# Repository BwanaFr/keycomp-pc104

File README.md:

# keycomp-pc104
A PC/104 compatible motherboard for Keycomp 386SX computer

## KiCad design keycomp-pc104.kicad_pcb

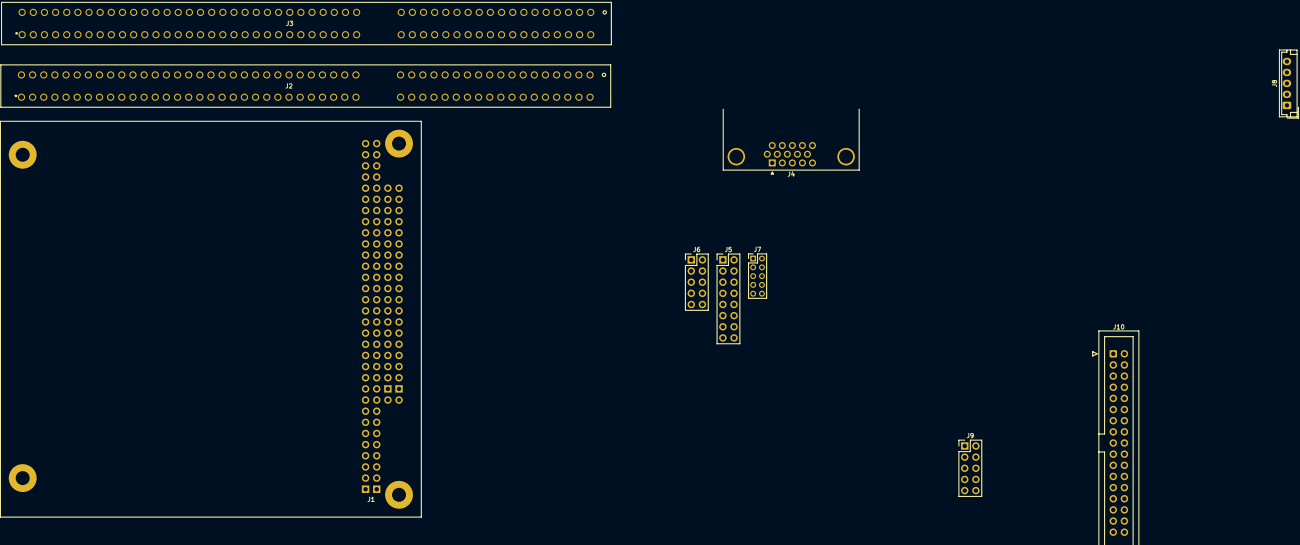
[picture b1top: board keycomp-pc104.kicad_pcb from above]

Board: 2 copper layers, 10 parts (0 on the bottom side), 101 nets, no tracks yet.

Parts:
J1: Bus_PC104_16bit; PC104_16bit
J2, J3: Bus_ISA_16bit; EBC49DCWN-S420
J4: VGA; DSUB-15-HD_Female_Horizontal_P2.29x1.98mm_EdgePinOffset8.35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
J5: VGA_PCM; PinHeader_2x08_P2.54mm_Vertical
J6: X10_KONTRON; PinHeader_2x05_P2.54mm_Vertical
J7: VGA_VORTEX; PinHeader_2x05_P2.00mm_Vertical
J8: KEYBOARD; JST_EH_B5B-EH-A_1x05_P2.50mm_Vertical
J9: X31_KONTRON; PinHeader_2x05_P2.54mm_Vertical
J10: FLOPPY; IDC-Header_2x17_P2.54mm_Vertical

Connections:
+5V: J1.B3 (+5V), J1.B29 (+5V), J1.D16 (+5V), J2.3 (+5V), J2.29 (VCC), J2.78 (+5V), J3.3 (+5V), J3.29 (VCC), J3.78 (+5V), J8.4
+12V: J1.B9 (+12V), J2.9 (+12V), J3.9 (+12V)
-5V: J1.B5 (-5V), J2.5 (-5V), J3.5 (-5V)
-12V: J1.B7 (-12V), J2.7 (-12V), J3.7 (-12V)
/IO ports/KB_CLK: J8.1, J9.6
/IO ports/KB_DATA: J8.2, J9.5
/IO ports/VGA_BLUE: J4.3, J5.5, J6.6, J7.5
/IO ports/VGA_GREEN: J4.2, J5.3, J6.4, J7.3
/IO ports/VGA_HSYNC: J4.13, J5.10, J6.8, J7.7
/IO ports/VGA_RED: J4.1, J5.1, J6.2, J7.1
/IO ports/VGA_SCL: J4.15, J6.10
/IO ports/VGA_SDA: J4.12, J6.7
/IO ports/VGA_VSYNC: J4.14, J5.12, J6.9, J7.9
AEN: J1.A11 (AEN), J2.42 (AEN), J3.42 (AEN)
BALE: J1.B28 (BALE), J2.28 (ALE), J3.28 (ALE)
BCLK: J1.B20 (BCLK), J2.20 (CLK), J3.20 (CLK)
DRQ0: J1.D9 (DRQ0), J2.71 (DRQ0), J3.71 (DRQ0)
DRQ1: J1.B18 (DRQ1), J2.18 (DRQ1), J3.18 (DRQ1)
DRQ2: J1.B6 (DRQ2), J2.6 (DRQ2), J3.6 (DRQ2)
DRQ3: J1.B16 (DRQ3), J2.16 (DRQ3), J3.16 (DRQ3)
DRQ5: J1.D11 (DRQ5), J2.73 (DRQ5), J3.73 (DRQ5)
DRQ6: J1.D13 (DRQ6), J2.75 (DRQ6), J3.75 (DRQ6)
DRQ7: J1.D15 (DRQ7), J2.77 (DRQ7), J3.77 (DRQ7)
GND: J1.A32 (GND), J1.B1 (GND), J1.B31 (GND), J1.B32 (GND), J1.C0 (GND), J1.D0 (GND), J1.D18 (GND), J1.D19 (GND), J2.31 (GND), J3.31 (GND), J4.0, J4.5, J4.6, J4.7, J4.8, J4.10, J5.4, J5.9, J5.11, J5.13, J5.15, J6.1, J7.2, J7.4, J7.6, J7.8, J7.10, J8.3, J9.7, J10.1, J10.3, J10.5, J10.7, J10.9, J10.11, J10.13, J10.15, J10.17, J10.19, J10.21, J10.23, J10.25, J10.27, J10.29, J10.31, J10.33
IOCHRDY: J1.A10 (IOCHRDY), J2.41 (IO_READY), J3.41 (IO_READY)
IRQ3: J1.B25 (IRQ3), J2.25 (IRQ3), J3.25 (IRQ3)
IRQ4: J1.B24 (IRQ4), J2.24 (IRQ4), J3.24 (IRQ4)
IRQ5: J1.B23 (IRQ5), J2.23 (IRQ5), J3.23 (IRQ5)
IRQ6: J1.B22 (IRQ6), J2.22 (IRQ6), J3.22 (IRQ6)
IRQ7: J1.B21 (IRQ7), J2.21 (IRQ7), J3.21 (IRQ7)
IRQ9: J1.B4 (IRQ9), J2.4 (IRQ2), J3.4 (IRQ2)
IRQ10: J1.D3 (IRQ10), J2.65 (IRQ10), J3.65 (IRQ10)
IRQ11: J1.D4 (IRQ11), J2.66 (IRQ11), J3.66 (IRQ11)
IRQ12: J1.D5 (IRQ12), J2.67 (IRQ12), J3.67 (IRQ12)
IRQ14: J1.D7 (IRQ14), J2.69 (IRQ14), J3.69 (IRQ14)
IRQ15: J1.D6 (IRQ15), J2.68 (IRQ15), J3.68 (IRQ15)
LA17: J1.C8 (LA17), J2.88 (LA17), J3.88 (LA17)
LA18: J1.C7 (LA18), J2.87 (LA18), J3.87 (LA18)
LA19: J1.C6 (LA19), J2.86 (LA19), J3.86 (LA19)
LA20: J1.C5 (LA20), J2.85 (LA20), J3.85 (LA20)
LA21: J1.C4 (LA21), J2.84 (LA21), J3.84 (LA21)
LA22: J1.C3 (LA22), J2.83 (LA22), J3.83 (LA22)
LA23: J1.C2 (LA23), J2.82 (LA23), J3.82 (LA23)
OSC: J1.B30 (OSC), J2.30 (OSC), J3.30 (OSC)
RESET: J1.B2 (RESET), J2.2 (RESET), J3.2 (RESET)
SA0: J1.A31 (SA0), J2.62 (BA00), J3.62 (BA00)
SA1: J1.A30 (SA1), J2.61 (BA01), J3.61 (BA01)
SA2: J1.A29 (SA2), J2.60 (BA02), J3.60 (BA02)
SA3: J1.A28 (SA3), J2.59 (BA03), J3.59 (BA03)
SA4: J1.A27 (SA4), J2.58 (BA04), J3.58 (BA04)
SA5: J1.A26 (SA5), J2.57 (BA05), J3.57 (BA05)
SA6: J1.A25 (SA6), J2.56 (BA06), J3.56 (BA06)
SA7: J1.A24 (SA7), J2.55 (BA07), J3.55 (BA07)
SA8: J1.A23 (SA8), J2.54 (BA08), J3.54 (BA08)
SA9: J1.A22 (SA9), J2.53 (BA09), J3.53 (BA09)
SA10: J1.A21 (SA10), J2.52 (BA10), J3.52 (BA10)
SA11: J1.A20 (SA11), J2.51 (BA11), J3.51 (BA11)
SA12: J1.A19 (SA12), J2.50 (BA12), J3.50 (BA12)
SA13: J1.A18 (SA13), J2.49 (BA13), J3.49 (BA13)
SA14: J1.A17 (SA14), J2.48 (BA14), J3.48 (BA14)
SA15: J1.A16 (SA15), J2.47 (BA15), J3.47 (BA15)
SA16: J1.A15 (SA16), J2.46 (BA16), J3.46 (BA16)
SA17: J1.A14 (SA17), J2.45 (BA17), J3.45 (BA17)
SA18: J1.A13 (SA18), J2.44 (BA18), J3.44 (BA18)
SA19: J1.A12 (SA19), J2.43 (BA19), J3.43 (BA19)
SD0: J1.A9 (SD0), J2.40 (DB0), J3.40 (DB0)
SD1: J1.A8 (SD1), J2.39 (DB1), J3.39 (DB1)
SD2: J1.A7 (SD2), J2.38 (DB2), J3.38 (DB2)
SD3: J1.A6 (SD3), J2.37 (DB3), J3.37 (DB3)
SD4: J1.A5 (SD4), J2.36 (DB4), J3.36 (DB4)
SD5: J1.A4 (SD5), J2.35 (DB5), J3.35 (DB5)
SD6: J1.A3 (SD6), J2.34 (DB6), J3.34 (DB6)
SD7: J1.A2 (SD7), J2.33 (DB7), J3.33 (DB7)
SD8: J1.C11 (SD8), J2.91 (D8), J3.91 (D8)
SD9: J1.C12 (SD9), J2.92 (D9), J3.92 (D9)
SD10: J1.C13 (SD10), J2.93 (D10), J3.93 (D10)
SD11: J1.C14 (SD11), J2.94 (D11), J3.94 (D11)
SD12: J1.C15 (SD12), J2.95 (D12), J3.95 (D12)
SD13: J1.C16 (SD13), J2.96 (D13), J3.96 (D13)
SD14: J1.C17 (SD14), J2.97 (D14), J3.97 (D14)
SD15: J1.C18 (SD15), J2.98 (D15), J3.98 (D15)
TC: J1.B27 (TC), J2.27 (TC), J3.27 (TC)
~DACK0: J1.D8 (~DACK0), J2.70 (~DACK0), J3.70 (~DACK0)
~DACK1: J1.B17 (~DACK1), J2.17 (~DACK1), J3.17 (~DACK1)
~DACK2: J1.B26 (~DACK2), J2.26 (~DACK2), J3.26 (~DACK2)
~DACK3: J1.B15 (~DACK3), J2.15 (~DACK3), J3.15 (~DACK3)
~DACK5: J1.D10 (~DACK5), J2.72 (~DACK5), J3.72 (~DACK5)
~DACK6: J1.D12 (~DACK6), J2.74 (~DACK6), J3.74 (~DACK6)
~DACK7: J1.D14 (~DACK7), J2.76 (~DACK7), J3.76 (~DACK7)
~IOC16: J1.D2 (~IOCS16), J2.64 (~IOCS16), J3.64 (~IOCS16)
~IOCHK: J1.A1 (~IOCHK), J2.32 (IO), J3.32 (IO)
~IOR: J1.B14 (~IOR), J2.14 (~IOR), J3.14 (~IOR)
~IOW: J1.B13 (~IOW), J2.13 (~IOW), J3.13 (~IOW)
~MASTER: J1.D17 (~MASTER), J2.79 (MASTER), J3.79 (MASTER)
~MEMCS16: J1.D1 (~MEMCS16), J2.63 (~MEMCS16), J3.63 (~MEMCS16)
~MEMR: J1.C9 (~MEMR), J2.89 (~MEMR), J3.89 (~MEMR)
~MEMW: J1.C10 (~MEMW), J2.90 (~MEMW), J3.90 (~MEMW)
~REFRESH: J1.B19 (~REFRESH), J2.19 (~REFRESH), J3.19 (~REFRESH)
~SBHE: J1.C1 (~SBHE), J2.81 (SBHE), J3.81 (SBHE)
~SMEMR: J1.B12 (~SMEMR), J2.12 (~SMEMR), J3.12 (~SMEMR)
~SMEMW: J1.B11 (~SMEMW), J2.11 (~SMEMW), J3.11 (~SMEMW)
